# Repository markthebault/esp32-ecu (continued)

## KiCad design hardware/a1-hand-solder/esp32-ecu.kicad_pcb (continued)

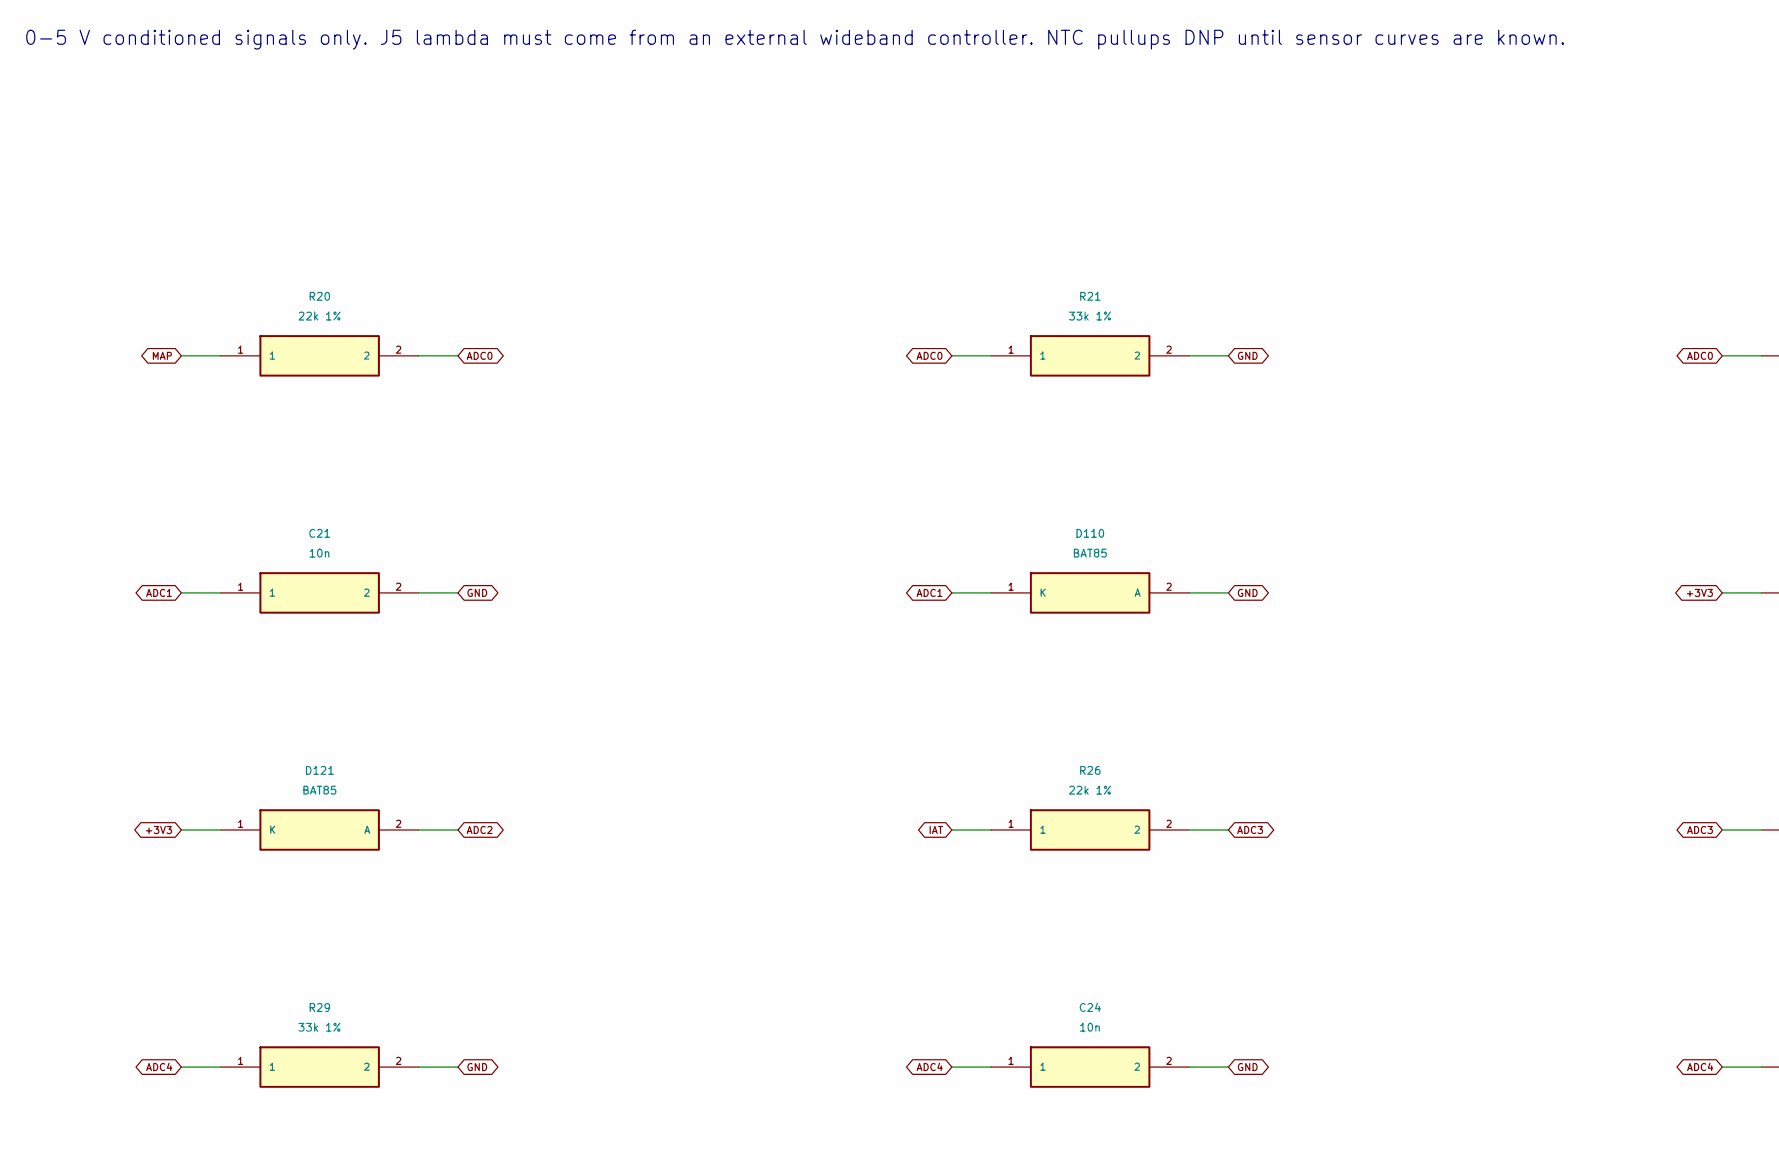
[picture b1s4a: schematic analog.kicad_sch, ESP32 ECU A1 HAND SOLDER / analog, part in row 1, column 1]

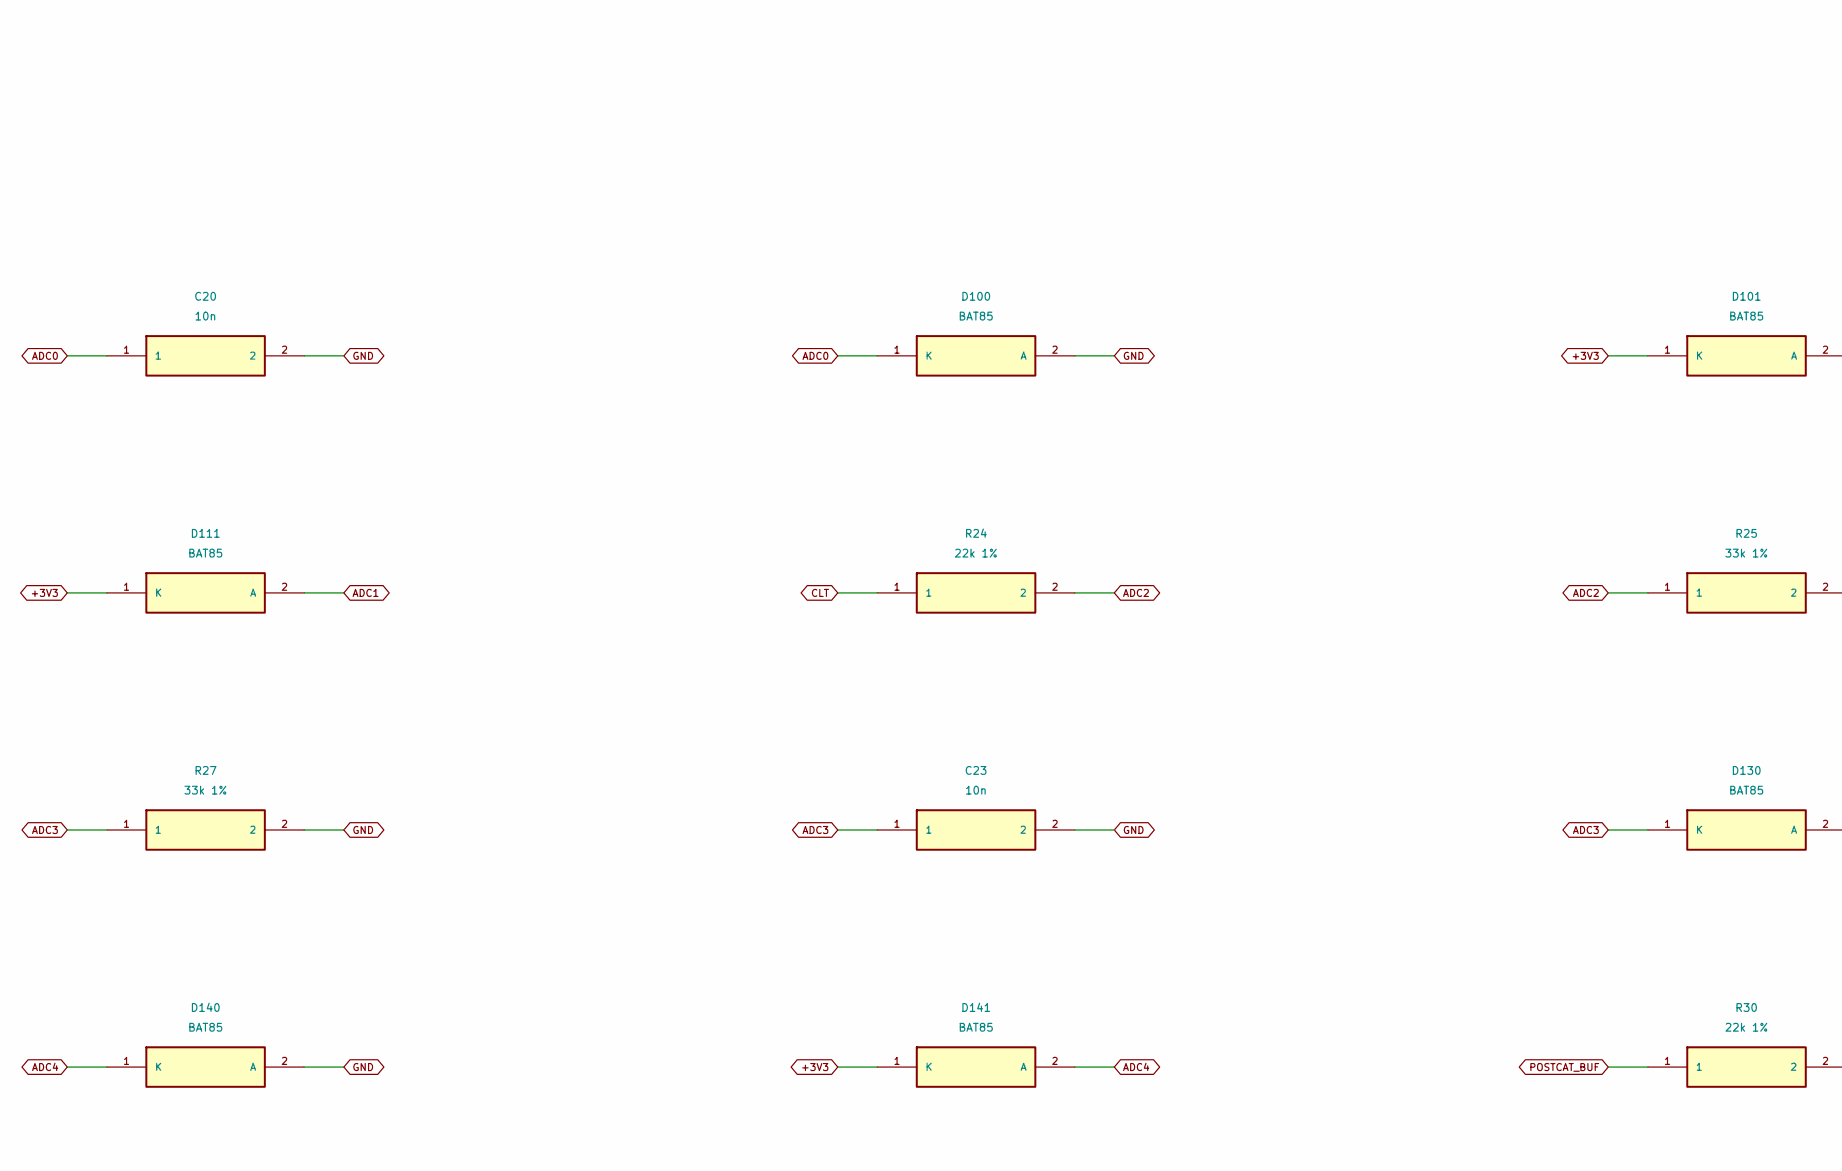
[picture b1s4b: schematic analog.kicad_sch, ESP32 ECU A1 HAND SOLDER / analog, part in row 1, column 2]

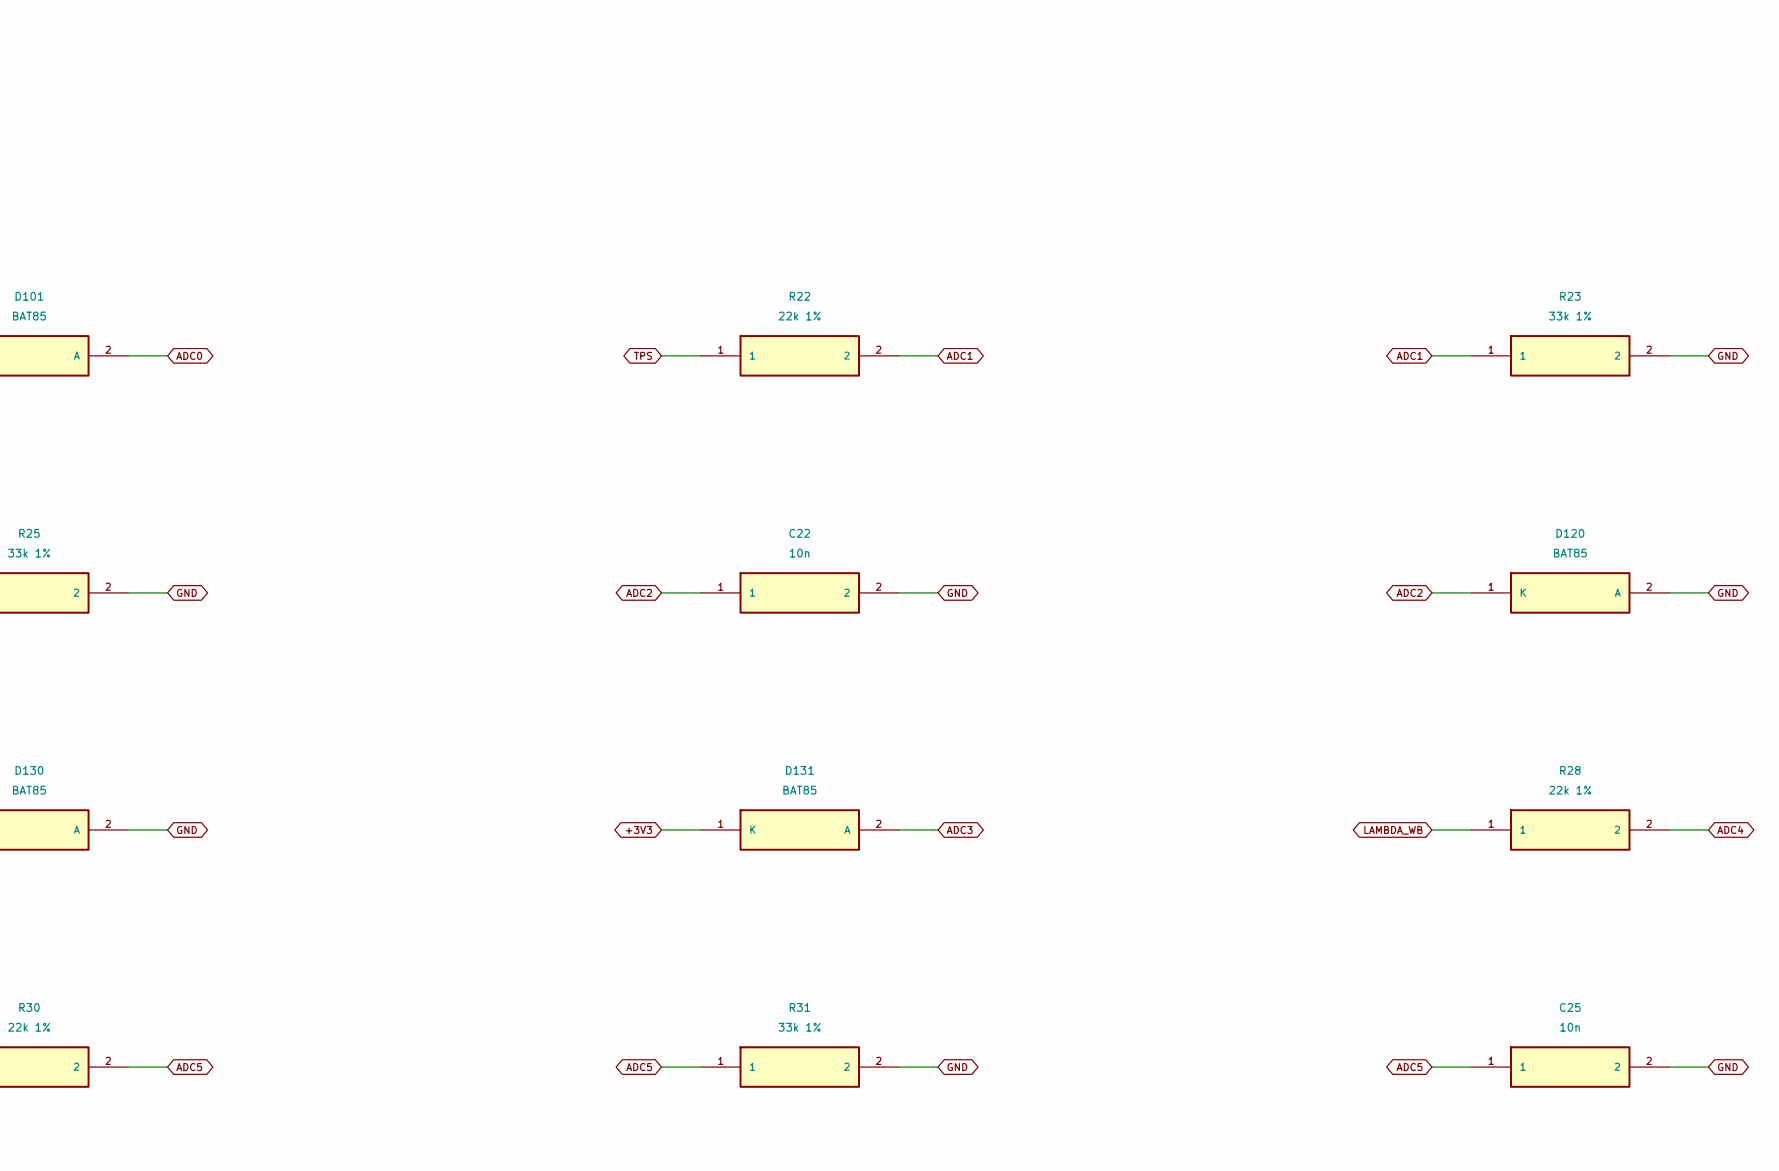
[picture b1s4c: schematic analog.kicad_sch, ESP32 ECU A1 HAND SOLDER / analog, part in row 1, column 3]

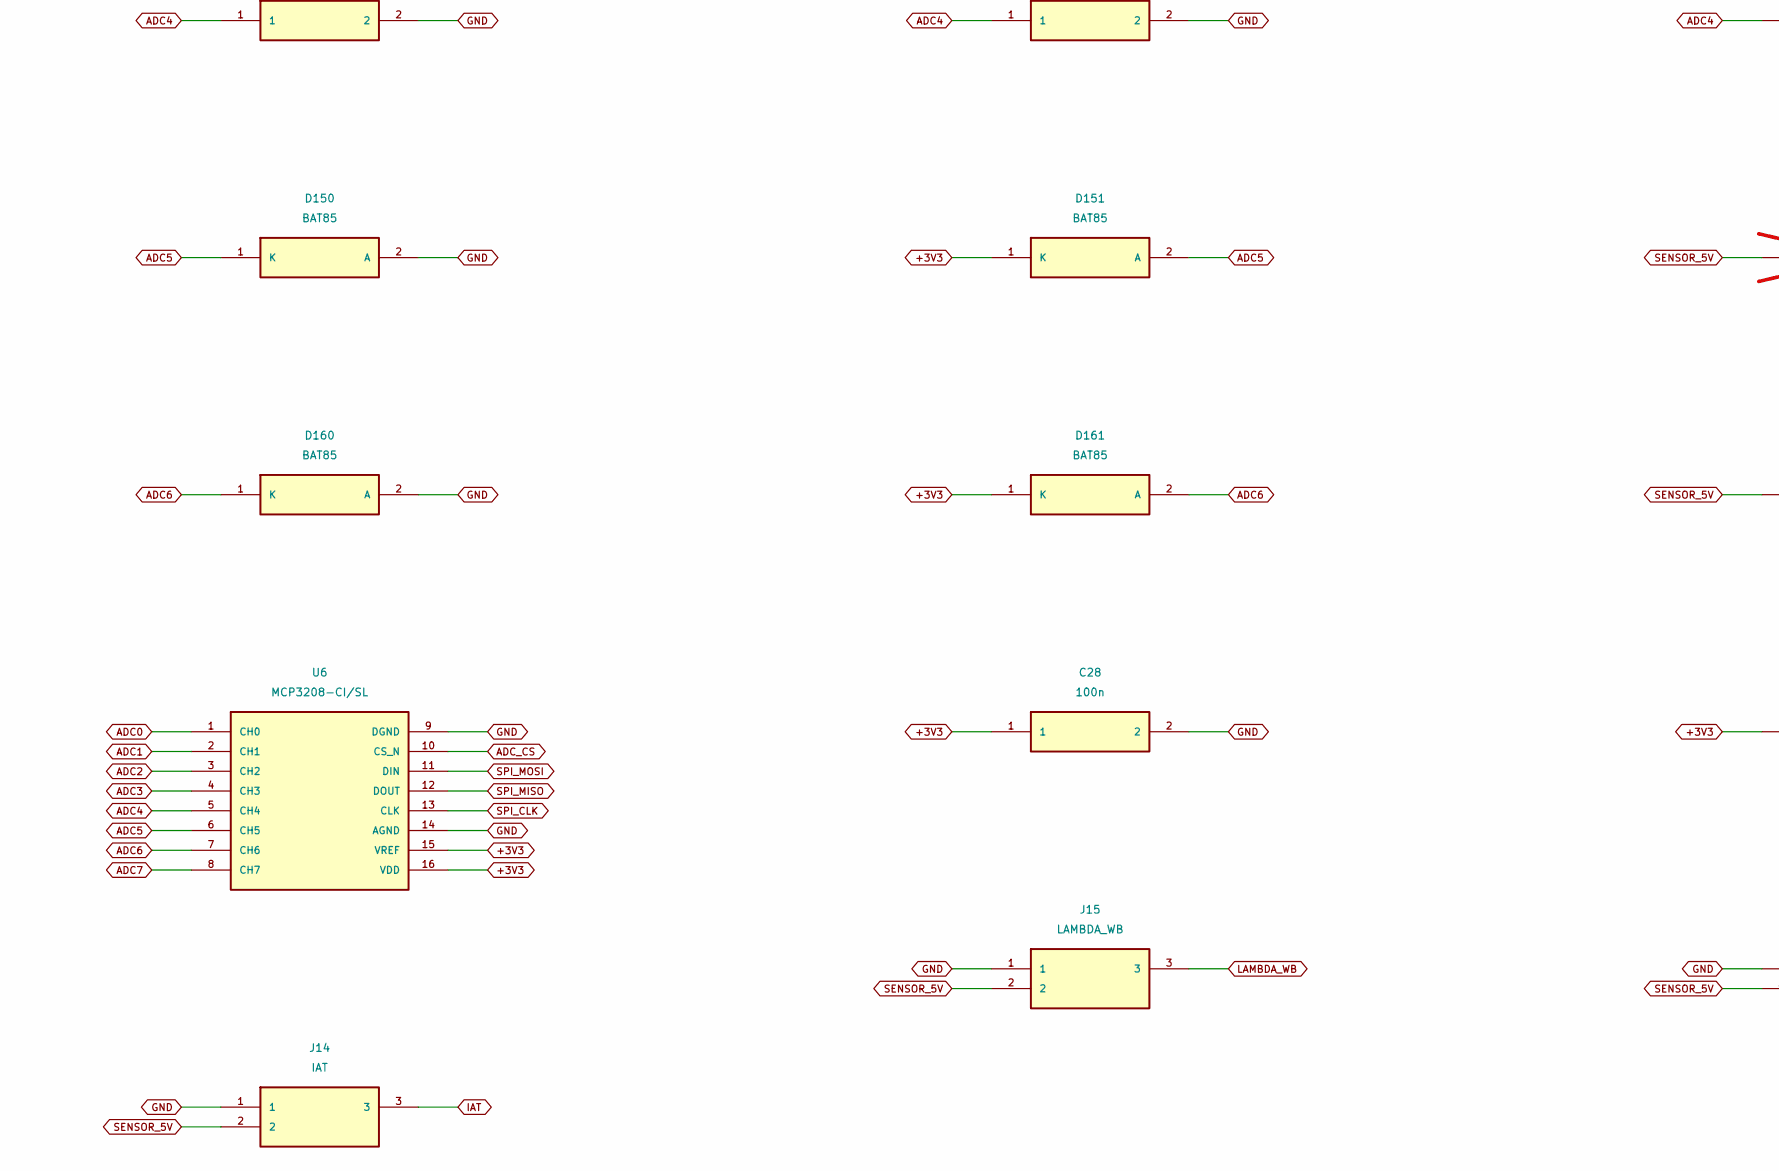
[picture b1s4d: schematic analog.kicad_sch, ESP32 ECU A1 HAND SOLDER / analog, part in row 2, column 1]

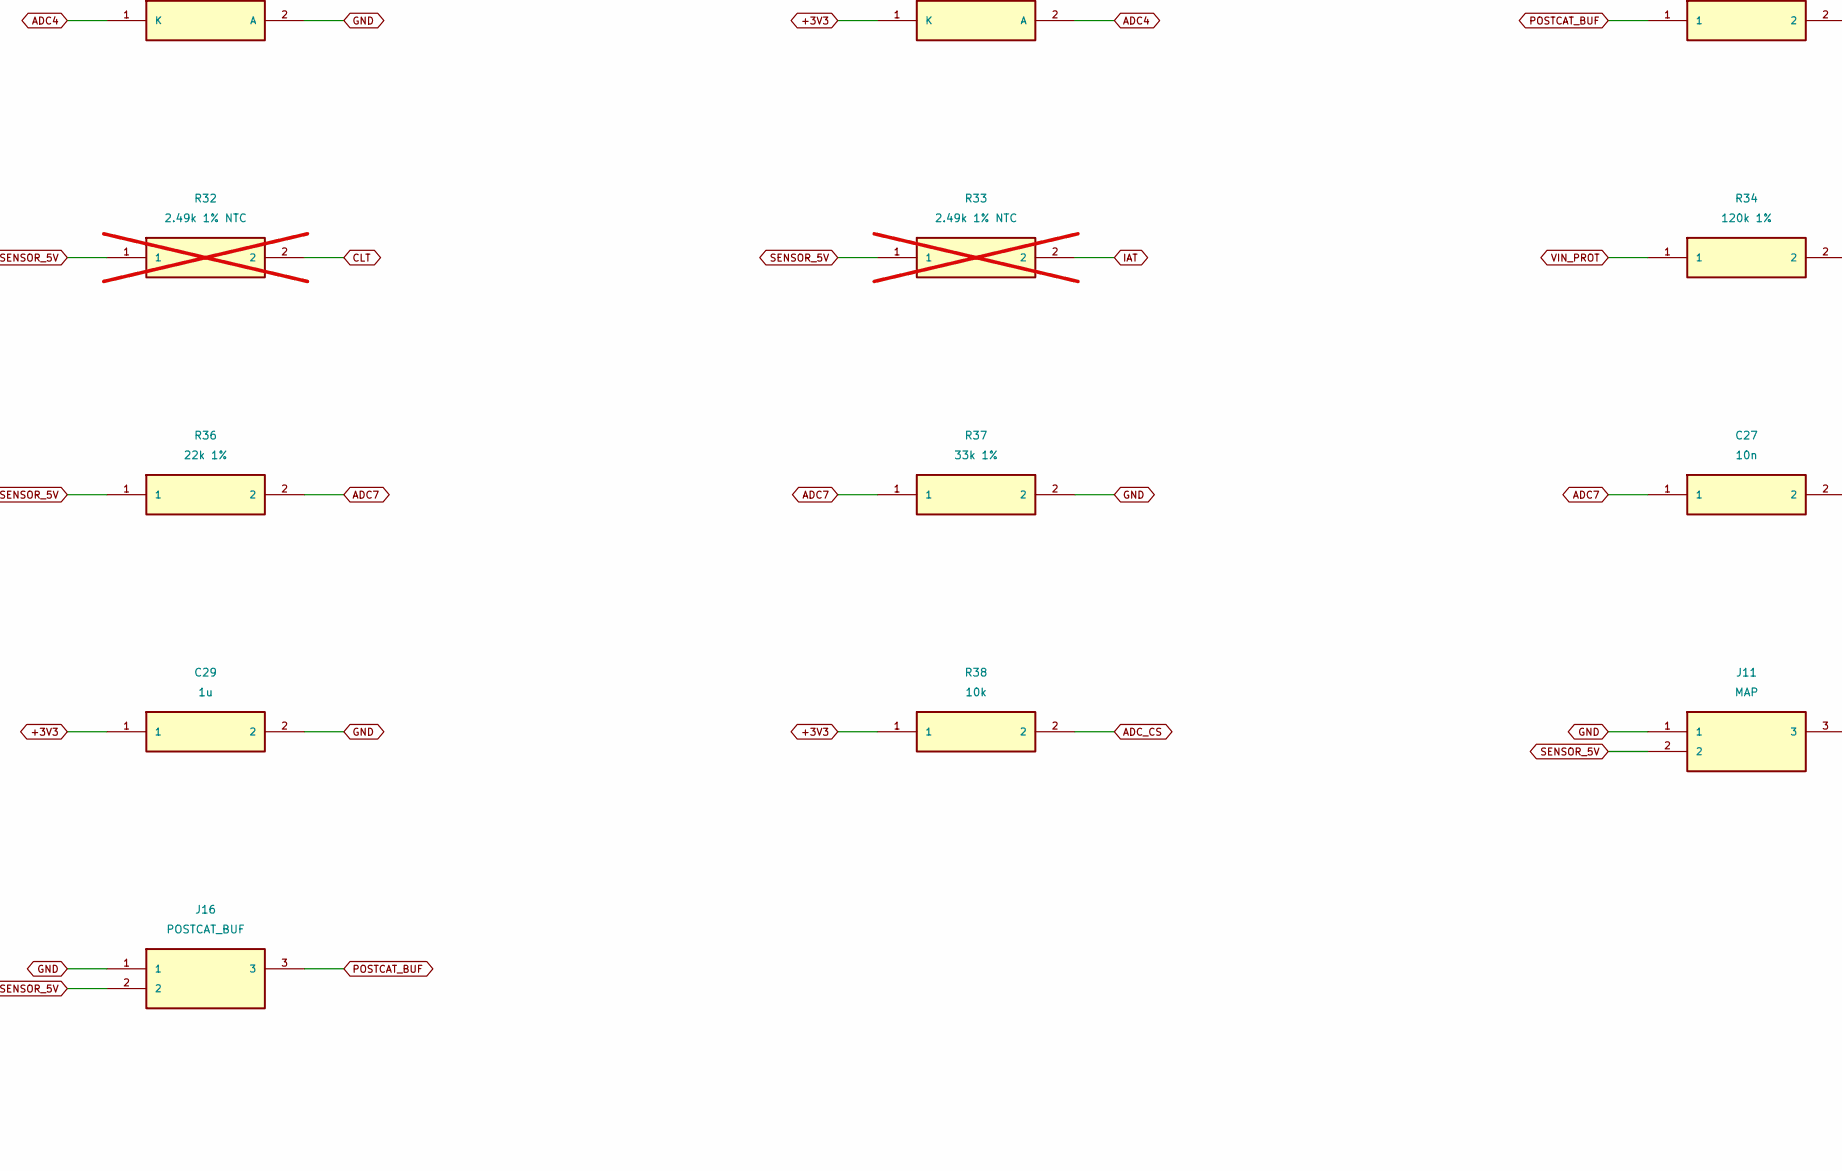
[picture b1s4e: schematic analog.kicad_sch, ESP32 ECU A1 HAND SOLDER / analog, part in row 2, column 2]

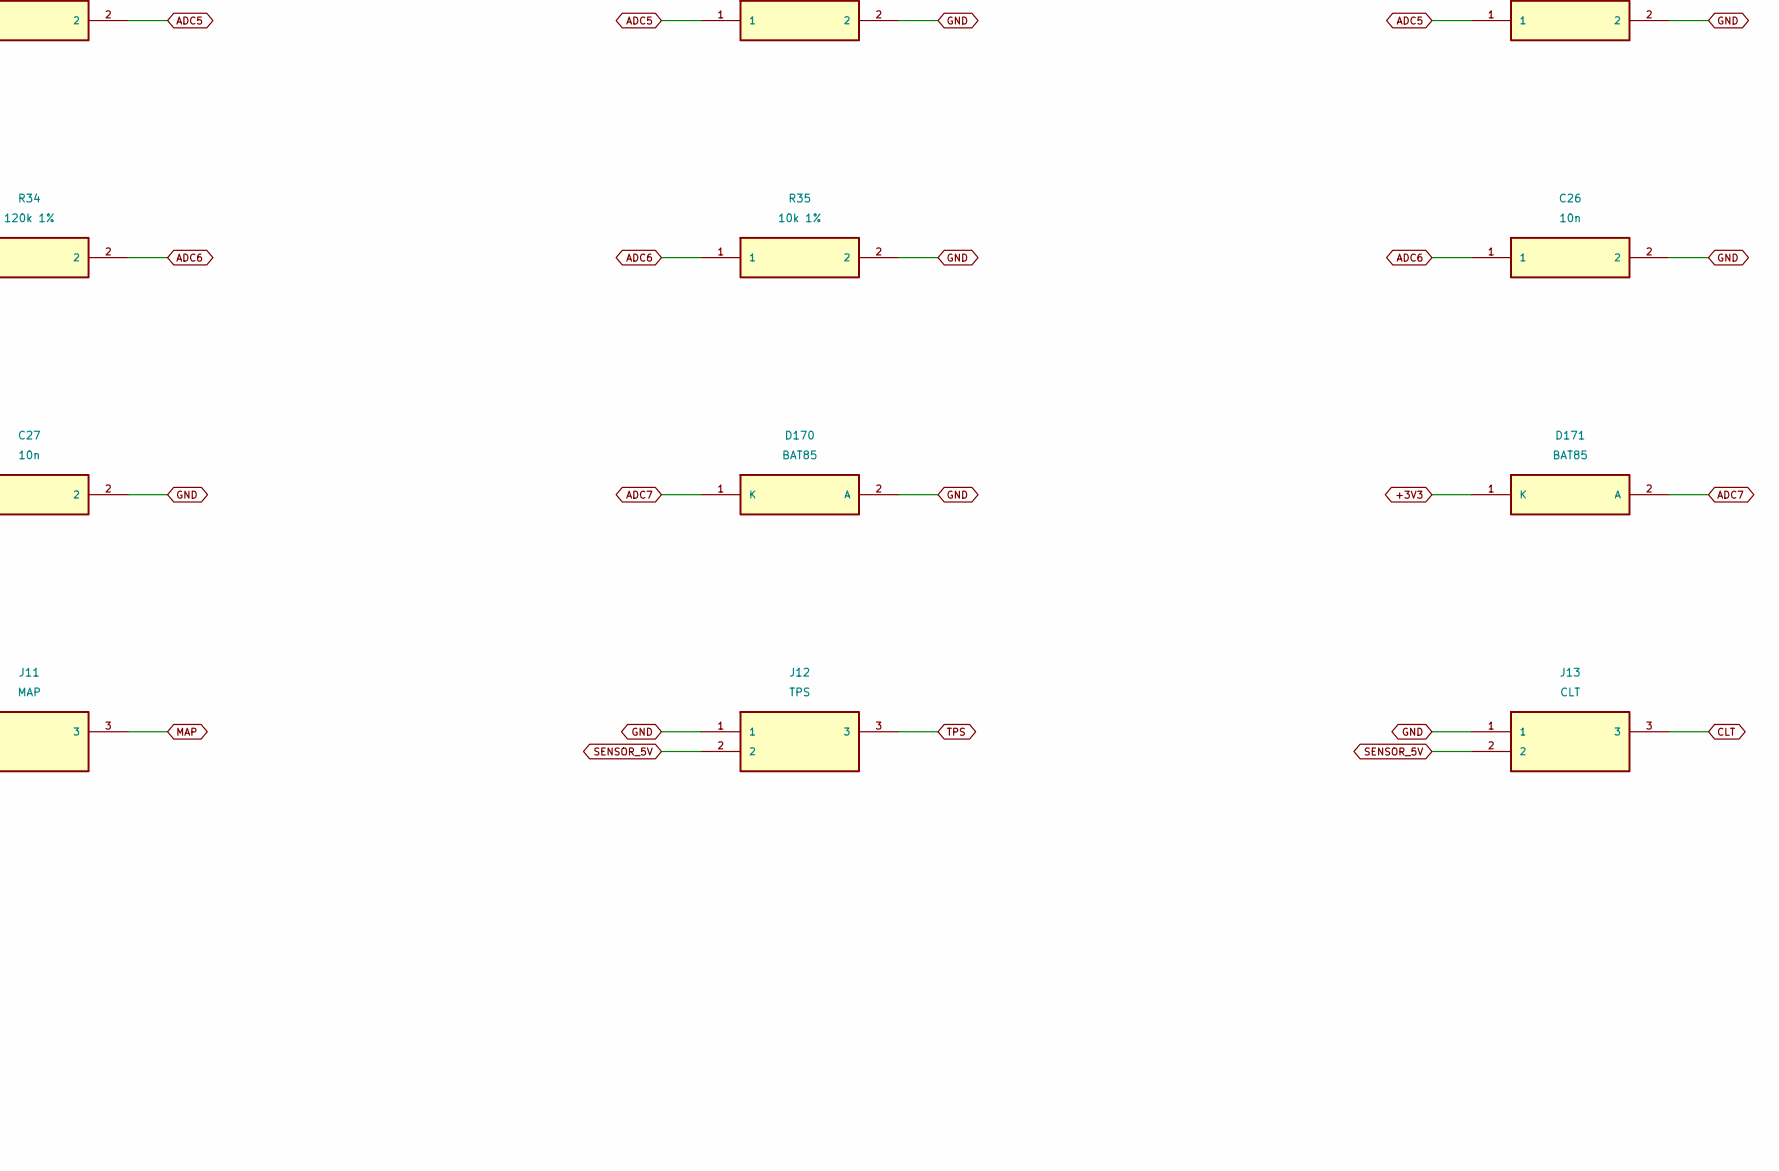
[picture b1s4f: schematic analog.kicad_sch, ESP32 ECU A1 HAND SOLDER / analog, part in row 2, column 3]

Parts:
C20, C21, C22, C23, C24, C25, C26, C27: 10n; C_1206_3216Metric_Pad1.33x1.80mm_HandSolder
C28: 100n; C_1206_3216Metric_Pad1.33x1.80mm_HandSolder
C29: 1u; C_1206_3216Metric_Pad1.33x1.80mm_HandSolder
D100, D101, D110, D111, D120, D121, D130, D131, D140, D141, D150, D151, D160, D161, D170, D171: BAT85; D_DO-35_SOD27_P3.81mm_Vertical_AnodeUp; MPN BAT85,113
J11: MAP; JST_XH_B3B-XH-A_1x03_P2.50mm_Vertical; MPN B3B-XH-A(LF)(SN)
J12: TPS; JST_XH_B3B-XH-A_1x03_P2.50mm_Vertical; MPN B3B-XH-A(LF)(SN)
J13: CLT; JST_XH_B3B-XH-A_1x03_P2.50mm_Vertical; MPN B3B-XH-A(LF)(SN)
J14: IAT; JST_XH_B3B-XH-A_1x03_P2.50mm_Vertical; MPN B3B-XH-A(LF)(SN)
J15: LAMBDA_WB; JST_XH_B3B-XH-A_1x03_P2.50mm_Vertical; MPN B3B-XH-A(LF)(SN)
J16: POSTCAT_BUF; JST_XH_B3B-XH-A_1x03_P2.50mm_Vertical; MPN B3B-XH-A(LF)(SN)
R20, R22, R24, R26, R28, R30, R36: 22k 1%; R_1206_3216Metric_Pad1.30x1.75mm_HandSolder
R21, R23, R25, R27, R29, R31, R37: 33k 1%; R_1206_3216Metric_Pad1.30x1.75mm_HandSolder
R32, R33: 2.49k 1% NTC; R_1206_3216Metric_Pad1.30x1.75mm_HandSolder; not fitted
R34: 120k 1%; R_1206_3216Metric_Pad1.30x1.75mm_HandSolder
R35: 10k 1%; R_1206_3216Metric_Pad1.30x1.75mm_HandSolder
R38: 10k; R_1206_3216Metric_Pad1.30x1.75mm_HandSolder
U6: MCP3208-CI/SL; SOIC-16_3.9x9.9mm_P1.27mm; MPN MCP3208-CI/SL

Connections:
+3V3: C28.1, C29.1, D101.1 (K), D111.1 (K), D121.1 (K), D131.1 (K), D141.1 (K), D151.1 (K), D161.1 (K), D171.1 (K), R38.1, U6.15 (VREF), U6.16 (VDD); also elsewhere on the board
ADC0: C20.1, D100.1 (K), D101.2 (A), R20.2, R21.1, U6.1 (CH0)
ADC1: C21.1, D110.1 (K), D111.2 (A), R22.2, R23.1, U6.2 (CH1)
ADC2: C22.1, D120.1 (K), D121.2 (A), R24.2, R25.1, U6.3 (CH2)
ADC3: C23.1, D130.1 (K), D131.2 (A), R26.2, R27.1, U6.4 (CH3)
ADC4: C24.1, D140.1 (K), D141.2 (A), R28.2, R29.1, U6.5 (CH4)
ADC5: C25.1, D150.1 (K), D151.2 (A), R30.2, R31.1, U6.6 (CH5)
ADC6: C26.1, D160.1 (K), D161.2 (A), R34.2, R35.1, U6.7 (CH6)
ADC7: C27.1, D170.1 (K), D171.2 (A), R36.2, R37.1, U6.8 (CH7)
ADC_CS: R38.2, U6.10 (CS_N); also elsewhere on the board
CLT: J13.3, R24.1, R32.2
GND: C20.2, C21.2, C22.2, C23.2, C24.2, C25.2, C26.2, C27.2, C28.2, C29.2, D100.2 (A), D110.2 (A), D120.2 (A), D130.2 (A), D140.2 (A), D150.2 (A), D160.2 (A), D170.2 (A), J11.1, J12.1, J13.1, J14.1, J15.1, J16.1, R21.2, R23.2, R25.2, R27.2, R29.2, R31.2, R35.2, R37.2, U6.9 (DGND), U6.14 (AGND); also elsewhere on the board
IAT: J14.3, R26.1, R33.2
LAMBDA_WB: J15.3, R28.1
MAP: J11.3, R20.1
POSTCAT_BUF: J16.3, R30.1
SENSOR_5V: J11.2, J12.2, J13.2, J14.2, J15.2, J16.2, R32.1, R33.1, R36.1; also elsewhere on the board
SPI_CLK: U6.13 (CLK); also elsewhere on the board
SPI_MISO: U6.12 (DOUT); also elsewhere on the board
SPI_MOSI: U6.11 (DIN); also elsewhere on the board
TPS: J12.3, R22.1
VIN_PROT: R34.1; also elsewhere on the board

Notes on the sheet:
0-5 V conditioned signals only. J5 lambda must come from an external wideband controller. NTC pullups DNP until sensor curves are known.

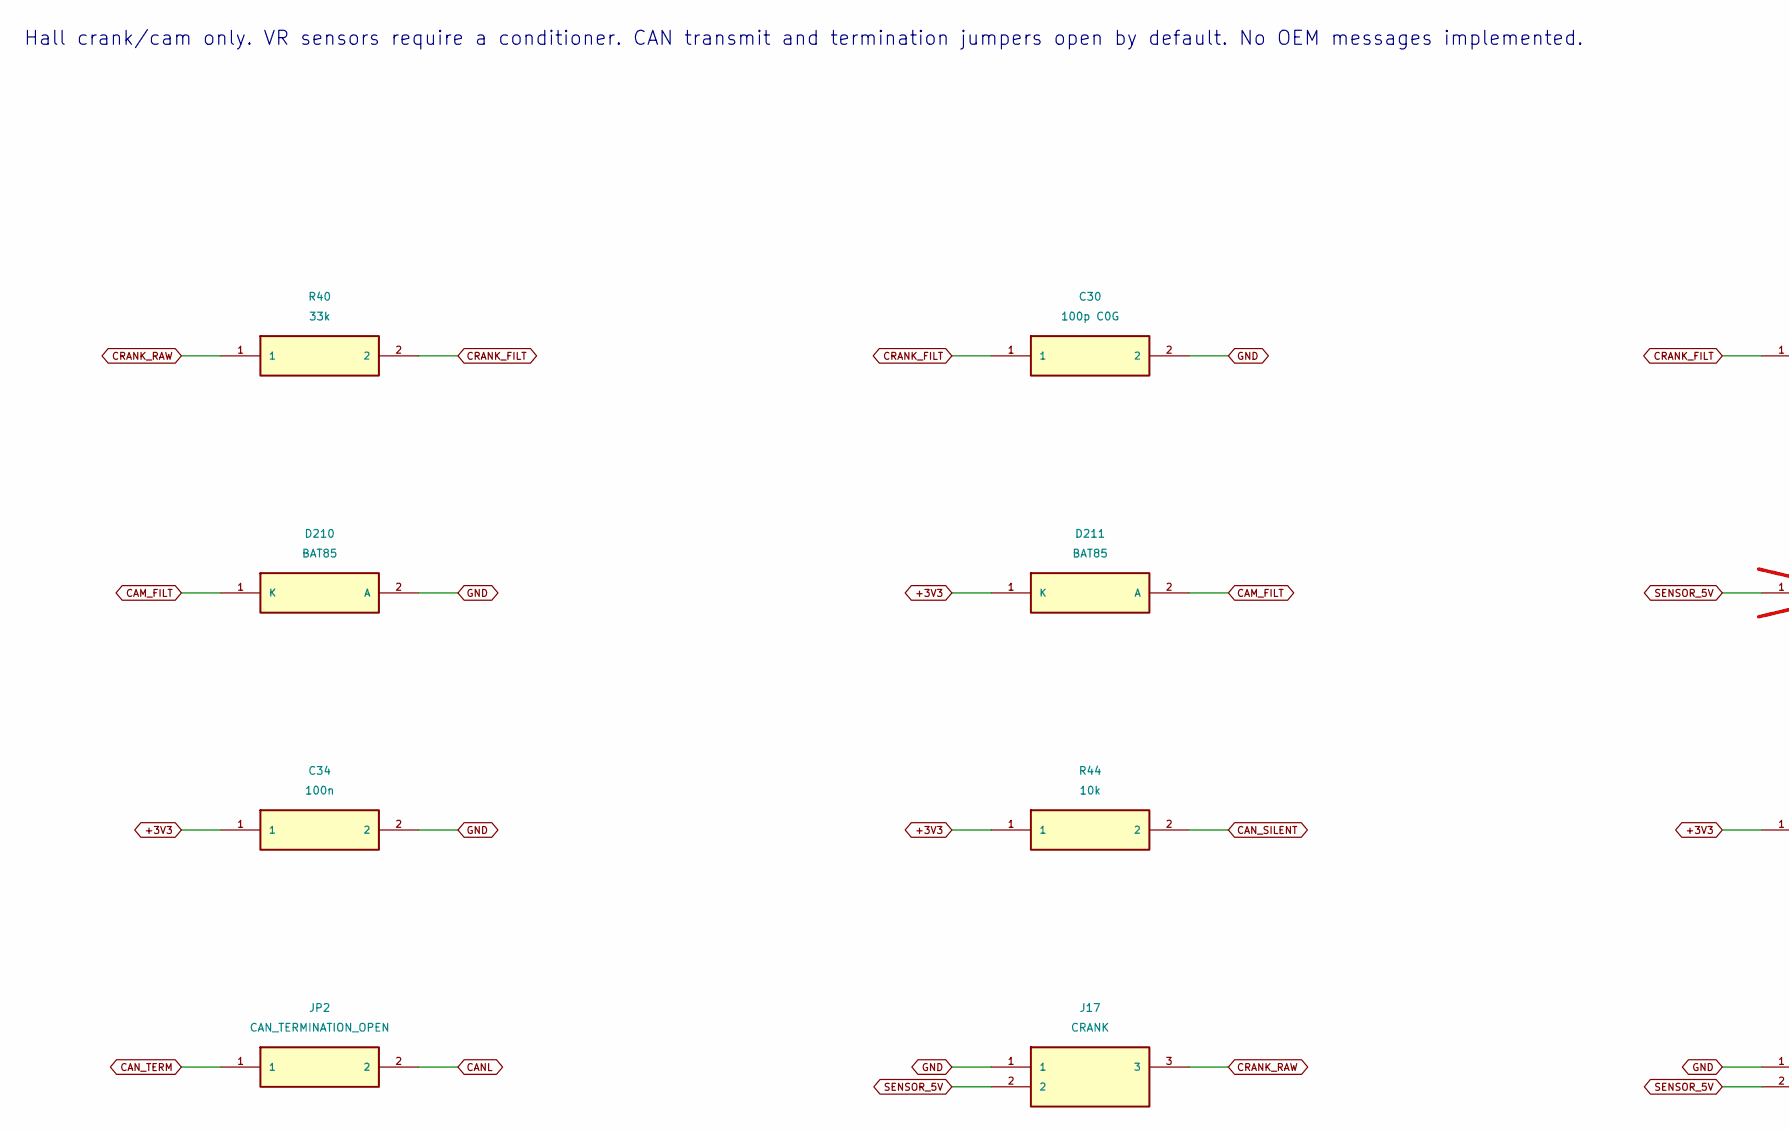
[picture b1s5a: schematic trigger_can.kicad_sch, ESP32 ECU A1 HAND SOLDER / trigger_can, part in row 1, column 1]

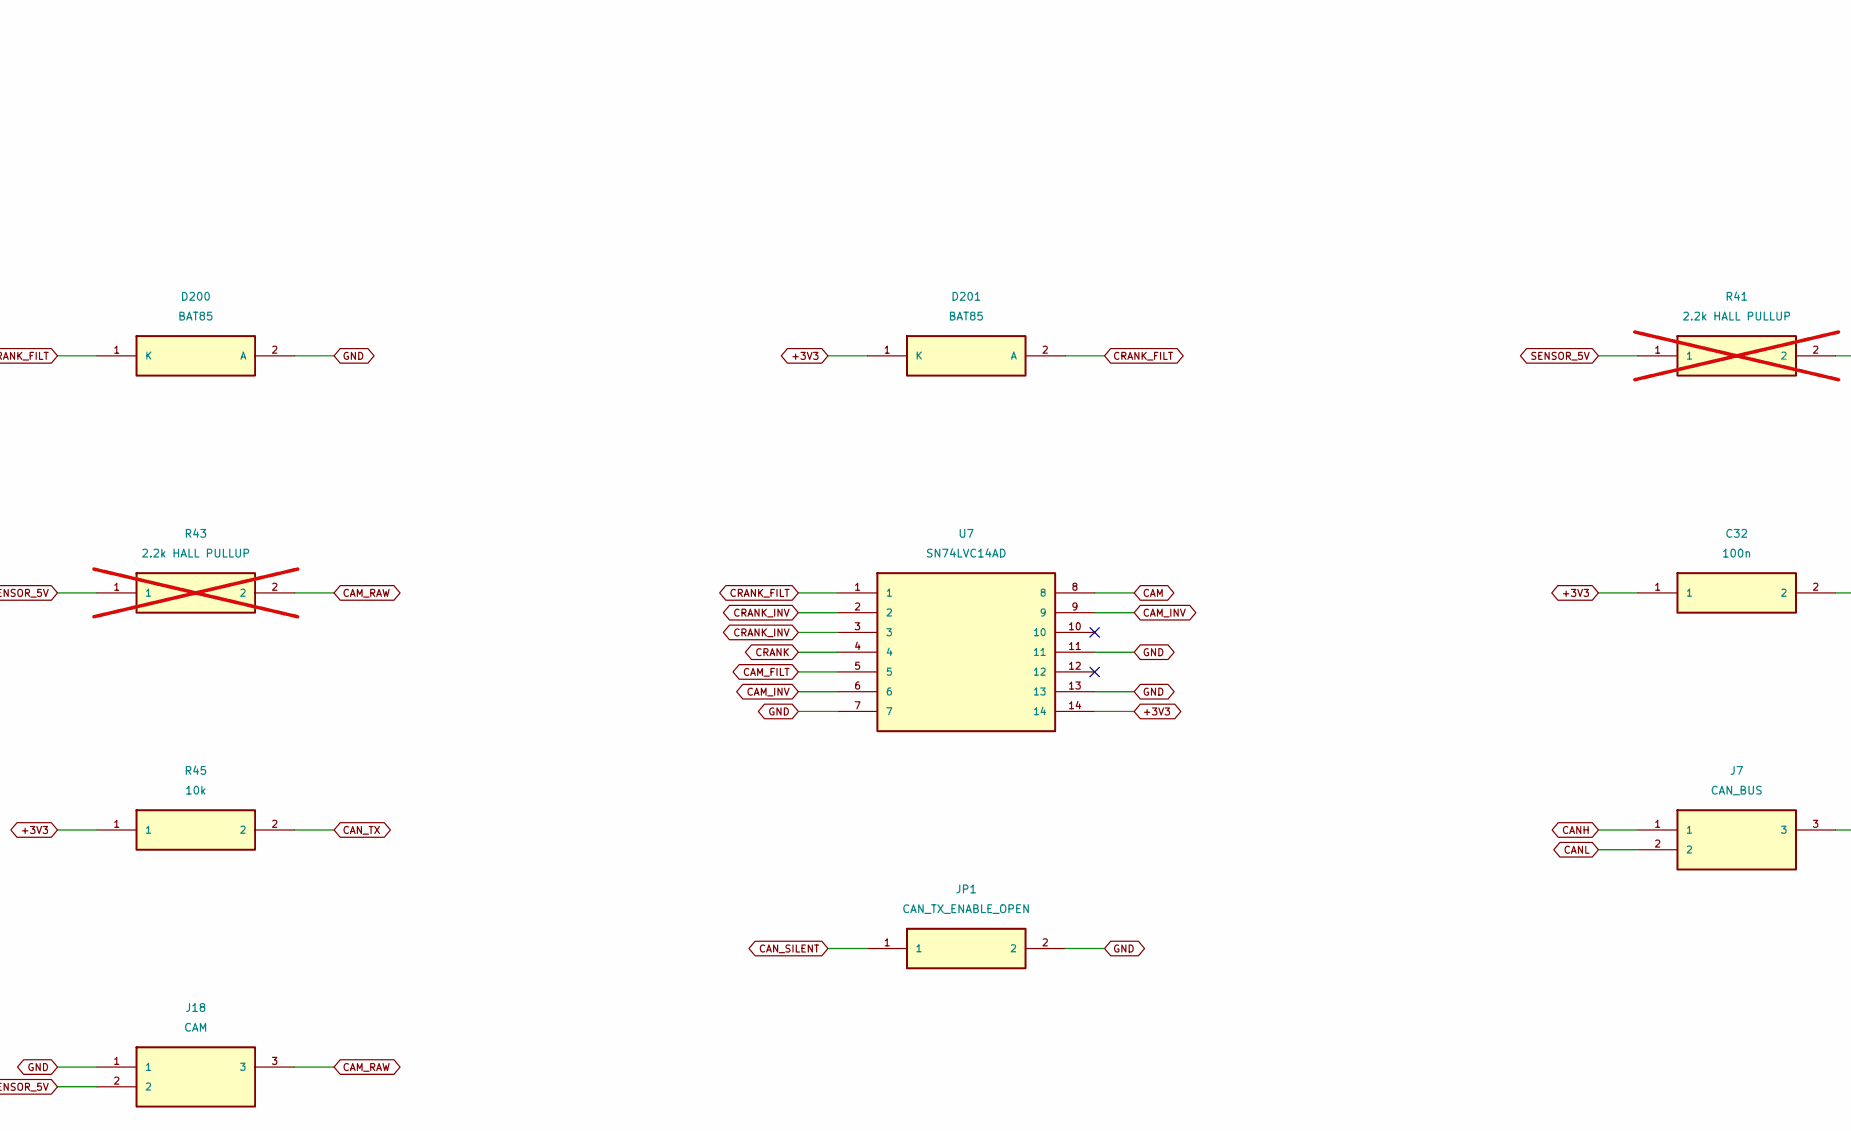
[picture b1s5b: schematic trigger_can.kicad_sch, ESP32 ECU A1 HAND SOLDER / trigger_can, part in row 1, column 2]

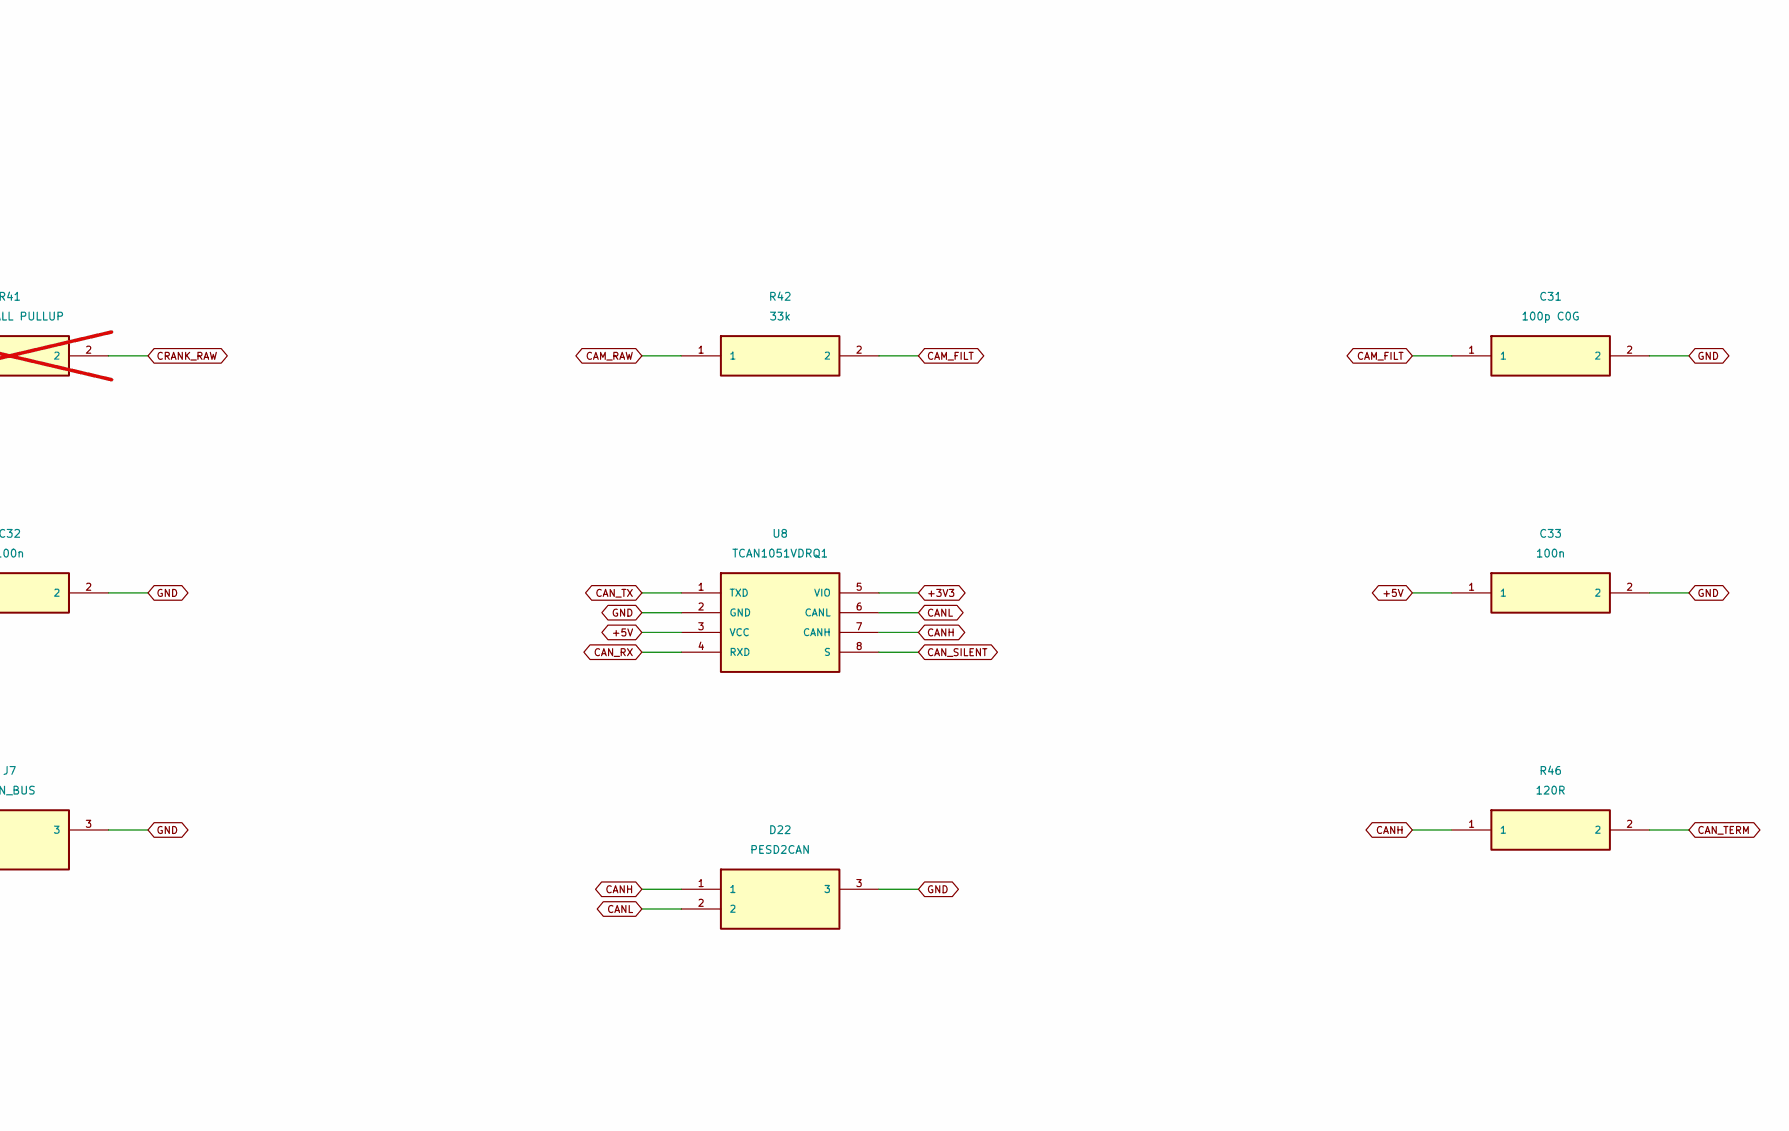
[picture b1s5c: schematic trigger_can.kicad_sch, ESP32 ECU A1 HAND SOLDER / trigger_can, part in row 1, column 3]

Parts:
C30, C31: 100p C0G; C_1206_3216Metric_Pad1.33x1.80mm_HandSolder
C32, C33, C34: 100n; C_1206_3216Metric_Pad1.33x1.80mm_HandSolder
D22: PESD2CAN; SOT-23; MPN PESD2CAN,215
D200, D201, D210, D211: BAT85; D_DO-35_SOD27_P3.81mm_Vertical_AnodeUp; MPN BAT85,113
J7: CAN_BUS; JST_XH_B3B-XH-A_1x03_P2.50mm_Vertical; MPN B3B-XH-A(LF)(SN)
J17: CRANK; JST_XH_B3B-XH-A_1x03_P2.50mm_Vertical; MPN B3B-XH-A(LF)(SN)
J18: CAM; JST_XH_B3B-XH-A_1x03_P2.50mm_Vertical; MPN B3B-XH-A(LF)(SN)
JP1: CAN_TX_ENABLE_OPEN; PinHeader_1x02_P2.54mm_Vertical
JP2: CAN_TERMINATION_OPEN; PinHeader_1x02_P2.54mm_Vertical
R40, R42: 33k; R_1206_3216Metric_Pad1.30x1.75mm_HandSolder
R41, R43: 2.2k HALL PULLUP; R_1206_3216Metric_Pad1.30x1.75mm_HandSolder; not fitted
R44, R45: 10k; R_1206_3216Metric_Pad1.30x1.75mm_HandSolder
R46: 120R; R_1206_3216Metric_Pad1.30x1.75mm_HandSolder
U7: SN74LVC14AD; SOIC-14_3.9x8.7mm_P1.27mm; MPN SN74LVC14AD
U8: TCAN1051VDRQ1; SOIC-8_3.9x4.9mm_P1.27mm; MPN TCAN1051VDRQ1

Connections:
+3V3: C32.1, C34.1, D201.1 (K), D211.1 (K), R44.1, R45.1, U7.14, U8.5 (VIO); also elsewhere on the board
+5V: C33.1, U8.3 (VCC); also elsewhere on the board
CAM: U7.8; also elsewhere on the board
CAM_FILT: C31.1, D210.1 (K), D211.2 (A), R42.2, U7.5
CAM_INV: U7.6, U7.9
CAM_RAW: J18.3, R42.1, R43.2
CANH: D22.1, J7.1, R46.1, U8.7 (CANH)
CANL: D22.2, J7.2, JP2.2, U8.6 (CANL)
CAN_RX: U8.4 (RXD); also elsewhere on the board
CAN_SILENT: JP1.1, R44.2, U8.8 (S)
CAN_TERM: JP2.1, R46.2
CAN_TX: R45.2, U8.1 (TXD); also elsewhere on the board
CRANK: U7.4; also elsewhere on the board
CRANK_FILT: C30.1, D200.1 (K), D201.2 (A), R40.2, U7.1
CRANK_INV: U7.2, U7.3
CRANK_RAW: J17.3, R40.1, R41.2
GND: C30.2, C31.2, C32.2, C33.2, C34.2, D22.3, D200.2 (A), D210.2 (A), J7.3, J17.1, J18.1, JP1.2, U7.7, U7.11, U7.13, U8.2 (GND); also elsewhere on the board
SENSOR_5V: J17.2, J18.2, R41.1, R43.1; also elsewhere on the board

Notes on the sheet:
Hall crank/cam only. VR sensors require a conditioner. CAN transmit and termination jumpers open by default. No OEM messages implemented.
